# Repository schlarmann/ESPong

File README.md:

# ESPong
PCB / Code for the ESP8266 Pong game. Based on the ESP Channel3 library

## File structure
 - pongCard: KiCad project for the pcb. Currently in Version 3
 - channel3Pong: Source code for ESPong itself. Code needs to refactored, it was written with / for cnlohr's SDK and then simply ported over to the arduino library.
 - channel3Image: Displays a static Image (Makerspace Minden logo). Comes with a converter script to convert pngs to header files.
 - channel3EtchASketch: Simple Etch-A-Sketch implementation for the pongCard. Demo board has rotating potentiometers instead of linear ones. Results are still "dotty" and there is no reset button to clear the screen

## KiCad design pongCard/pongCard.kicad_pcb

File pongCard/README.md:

# Pong card
PCB for ESPong3D

## BOM
| Reference          | Qty | Value               | Link                                                 | 
|--------------------|-----|---------------------|---|
| BT1, BT2           | 2   | AAA                 | https://www.lcsc.com/product-detail/Battery-Connectors_MYOUNG-BH-AAA-A1AJ001_C5290189.html |
| C1, C3, C8         | 3   | 100u                | https://www.lcsc.com/product-detail/Multilayer-Ceramic-Capacitors-MLCC-SMD-SMT_Samsung-Electro-Mechanics-CL31A107MQHNNNE_C15008.html |
| C4, C9, C2         | 2   | 100n                | https://www.lcsc.com/product-detail/Multilayer-Ceramic-Capacitors-MLCC-SMD-SMT_Walsin-Tech-Corp-0603B104K250CT_C83054.html |
| C5, C6             | 2   | 22p                 |  |
| C7                 | 1   | 100p                |  |
| D1                 | 1   | 1N5819              | https://www.lcsc.com/product-detail/Schottky-Barrier-Diodes-SBD_HXY-MOSFET-1N5819W_C5451628.html |
| J1                 | 1   | USB_B_Micro         | https://www.lcsc.com/product-detail/USB-Connectors_SHOU-HAN-MicroXNJ_C404969.html |
| L1                 | 1   | 47µ                 | https://www.lcsc.com/product-detail/Inductors-SMD_Sunlord-AWL3225FP470MTF_C2846230.html |
| R1, R2, R3, R4, R5 | 5   | 22k                 | https://www.lcsc.com/product-detail/Chip-Resistor-Surface-Mount_RALEC-RTT03223JTP_C103426.html |
| R6                 | 1   | 47R                 |  |
| RV1, RV2           | 2   | 10k // 100k         | https://www.lcsc.com/product-detail/Variable-Resistors-Potentiometers_ALPSALPINE-RS30H11AA009_C470610.html(or: https://www.pollin.de/p/schieberegler-30ld1c-b-cap5-100k-240836) |
| SW1                | 1   | SW_SPDT_COM         | https://www.lcsc.com/product-detail/Slide-Switches_SHOU-HAN-MSK12C02-HB_C431541.html |
| U2                 | 1   | HT7533-1-SOT89      | https://lcsc.com/product-detail/Linear-Voltage-Regulators-LDO_KEXIN-HT7533_C499633.html |
| U3                 | 1   | ESP-12E             | https://www.lcsc.com/product-detail/WiFi-Modules_Ai-Thinker-ESP-12F-ESP8266MOD_C82891.html |
| U4                 | 1   | QX2303L33E          | https://www.lcsc.com/product-detail/DC-DC-Converters_QX-Micro-Devices-QX2303L33E_C236071.html |

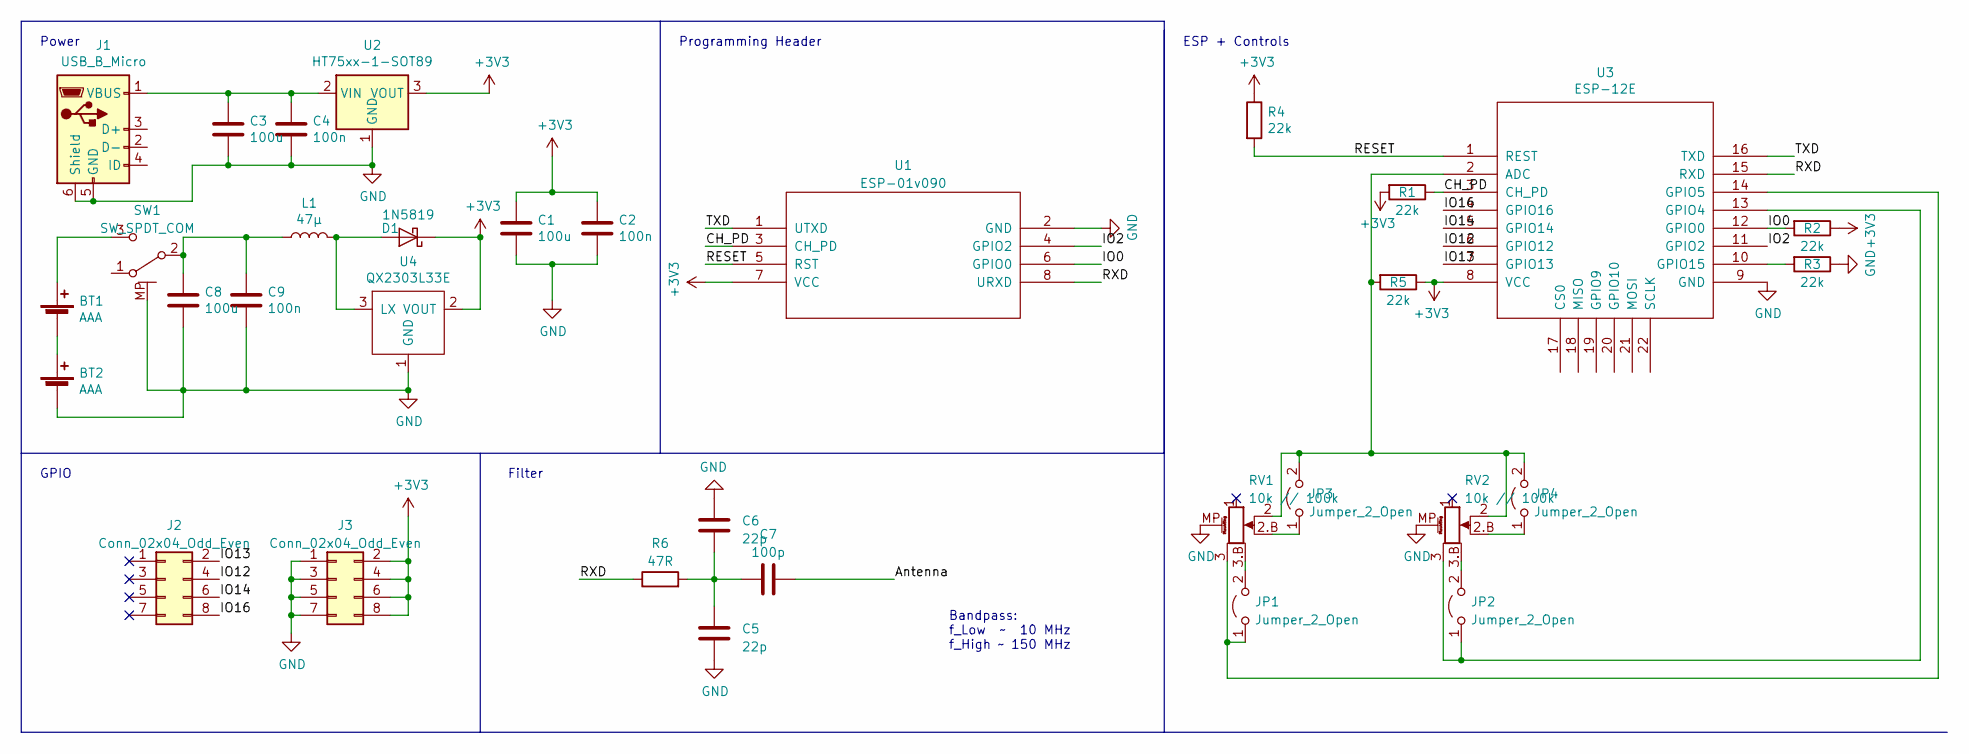
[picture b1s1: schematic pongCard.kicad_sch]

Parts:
BT1, BT2: AAA; BatteryHolder_AAA_MYOUNG
C1, C3, C8: 100u; C_1206_3216Metric_Pad1.33x1.80mm_HandSolder
C2, C4, C9: 100n; C_0603_1608Metric_Pad1.08x0.95mm_HandSolder
C5, C6: 22p; C_0603_1608Metric_Pad1.08x0.95mm_HandSolder
C7: 100p; C_0603_1608Metric_Pad1.08x0.95mm_HandSolder
D1: 1N5819; D_SOD-123
J1: USB_B_Micro; USB_Micro-B_Molex-105017-0001
J2, J3: Conn_02x04_Odd_Even; protoPins2x4
JP1, JP2, JP3, JP4: Jumper_2_Open; SolderJumper-2_P1.3mm_Open_RoundedPad1.0x1.5mm
L1: 47µ; L_1210_3225Metric_Pad1.42x2.65mm_HandSolder
R1, R2, R3, R4, R5: 22k; R_0603_1608Metric_Pad0.98x0.95mm_HandSolder
R6: 47R; R_0603_1608Metric_Pad0.98x0.95mm_HandSolder
RV1, RV2: 10k // 100k; linearPotentiometer
SW1: SW_SPDT_COM; SW_SPDT_PCM12_COM
U1: ESP-01v090; ESP-01
U2: HT75xx-1-SOT89; SOT-89-3_Handsoldering
U3: ESP-12E
U4: QX2303L33E; SOT-89-3_Handsoldering

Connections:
+3V3: C1.1, C2.1, D1.1 (K), J3.2, J3.4, J3.6, J3.8, R1.2, R2.1, R4.1, R5.1, U1.7 (VCC), U2.3 (VOUT), U3.8 (VCC), U4.2 (VOUT)
/Antenna: C7.2
/CH_PD: R1.1, U1.3 (CH_PD), U3.3 (CH_PD)
/IO0: R2.2, U1.6 (GPIO0), U3.12 (GPIO0)
/IO2: U1.4 (GPIO2), U3.11 (GPIO2)
/IO12: J2.4, U3.6 (GPIO12)
/IO13: J2.2, U3.7 (GPIO13)
/IO14: J2.6, U3.5 (GPIO14)
/IO16: J2.8, U3.4 (GPIO16)
/RESET: R4.2, U1.5 (RST), U3.1 (REST)
/RXD: R6.1, U1.8 (URXD), U3.15 (RXD)
/TXD: U1.1 (UTXD), U3.16 (TXD)
GND: BT2.2 (-), C1.2, C2.2, C3.2, C4.2, C5.2, C6.1, C8.2, C9.2, J1.5 (GND), J1.6 (Shield), J3.1, J3.3, J3.5, J3.7, R3.1, RV1.MP (MountPin), RV2.MP (MountPin), SW1.MP, U1.2 (GND), U2.1 (GND), U3.9 (GND), U4.1 (GND)
unnamed: BT1.1 (+), SW1.3 (C)
unnamed: BT1.2 (-), BT2.1 (+)
unnamed: C5.1, C6.2, C7.1, R6.2
unnamed: D1.2 (A), L1.2, U4.3 (LX)
unnamed: C3.1, C4.1, J1.1 (VBUS), U2.2 (VIN)
unnamed: JP1.1 (A), RV1.3, U3.14 (GPIO5)
unnamed: JP1.2 (B), RV1.3.B
unnamed: JP2.1 (A), RV2.3, U3.13 (GPIO4)
unnamed: JP2.2 (B), RV2.3.B
unnamed: JP3.1 (A), RV1.2.B
unnamed: JP3.2 (B), JP4.2 (B), R5.2, RV1.2, RV2.2, U3.2 (ADC)
unnamed: JP4.1 (A), RV2.2.B
unnamed: C8.1, C9.1, L1.1, SW1.2 (B)
unnamed: R3.2, U3.10 (GPIO15)

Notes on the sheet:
GPIO
Bandpass: f_Low ~ 10 MHz f_High ~ 150 MHz
Programming Header
Filter
ESP + Controls
Power

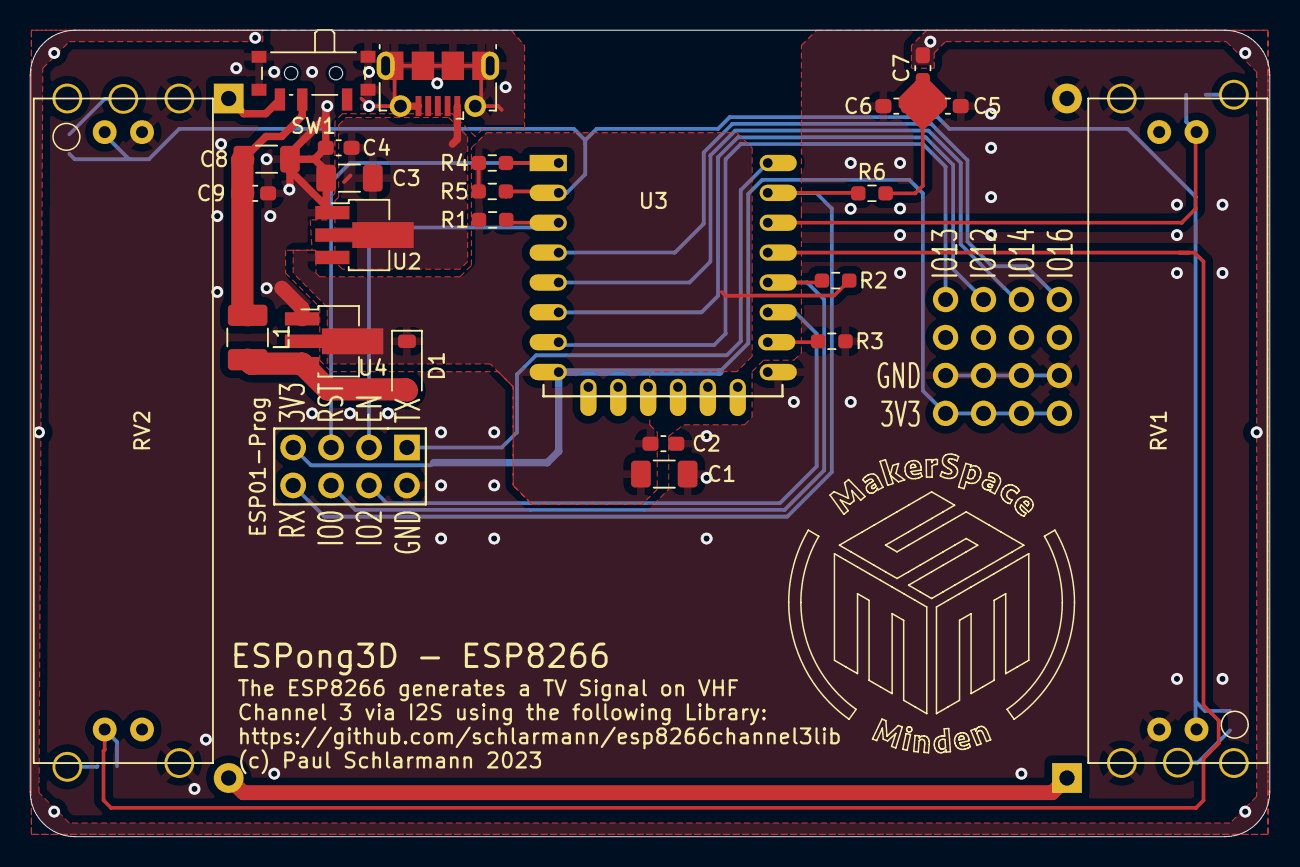
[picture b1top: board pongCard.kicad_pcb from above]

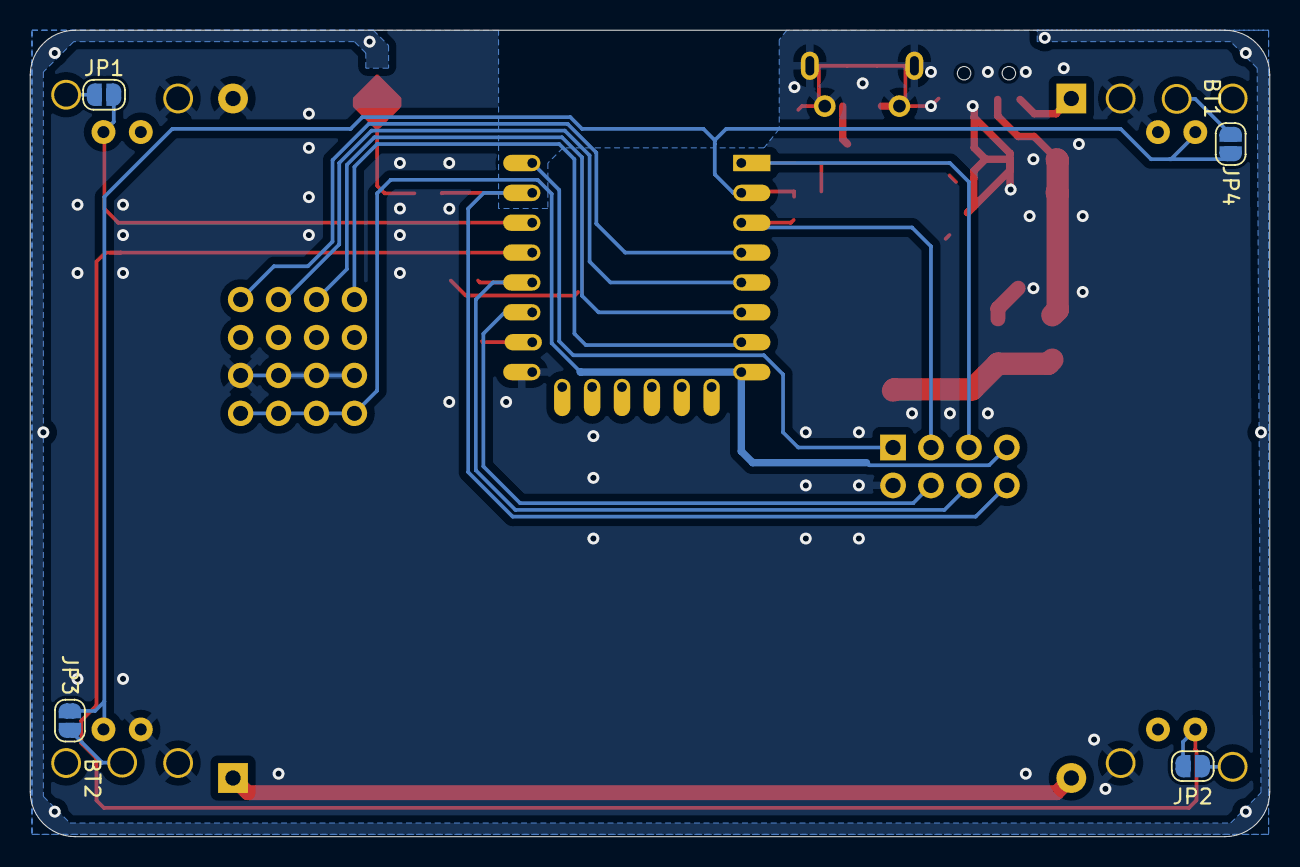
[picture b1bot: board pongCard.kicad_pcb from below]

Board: 2 copper layers, 83.0 x 54.0 mm, 34 parts (6 on the bottom side), 26 nets.

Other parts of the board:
LogoCu**: LogoCu

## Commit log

2023-07-24 INIT: Added V2 (current SOP)
2023-07-24 V3: Battery Step up
2023-08-17 Added source code: - channel3EtchASketch: Etch-A-Sketch implementation on the pong card - channel3Image: Static Image - channel3Pong: Source code for ESPong 3D
